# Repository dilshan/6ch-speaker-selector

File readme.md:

This project is a DIY six-channel stereo speaker selector based on *[STC15W201](https://www.stcmicro.com/datasheet/STC15W201S_Features.pdf)* MCU. The purpose of this electronic switch is to share a pair of speakers between six stereo audio systems.

To select each speaker channel, we use a couple of 12V DPDT relays. These relays interface to *74HC595* through a *ULN2001D*, 3-channel Darlington transistor array IC. 

The 6-channel speaker selector is an open-source project. This repository has all the schematics, PCB design files, and firmware source codes. 

The complete [documentation](https://github.com/dilshan/6ch-speaker-selector/wiki) of this project is in the [wiki section](https://github.com/dilshan/6ch-speaker-selector/wiki) of this repository. The PCB Gerber files and compiled binaries are also available in the [release section](https://github.com/dilshan/6ch-speaker-selector/releases) of this repository. The PCB of the 6-channel speaker selector can also order from the [PCBWay website](https://www.pcbway.com/project/shareproject/6_channel_stereo_speaker_selector_a32e4deb.html).

This is a [certified open hardware project](https://certification.oshwa.org/lk000013.html) and all the content of this project is distributed under the terms of the following license:

- Hardware License: [CERN-OHL-W 2.0](https://ohwr.org/cern_ohl_w_v2.txt)
- Software License: [MIT](https://github.com/dilshan/6ch-speaker-selector/blob/main/LICENSE)
- [Documentation](https://github.com/dilshan/6ch-speaker-selector/wiki) License: [CC BY 4.0](https://creativecommons.org/licenses/by/4.0/)

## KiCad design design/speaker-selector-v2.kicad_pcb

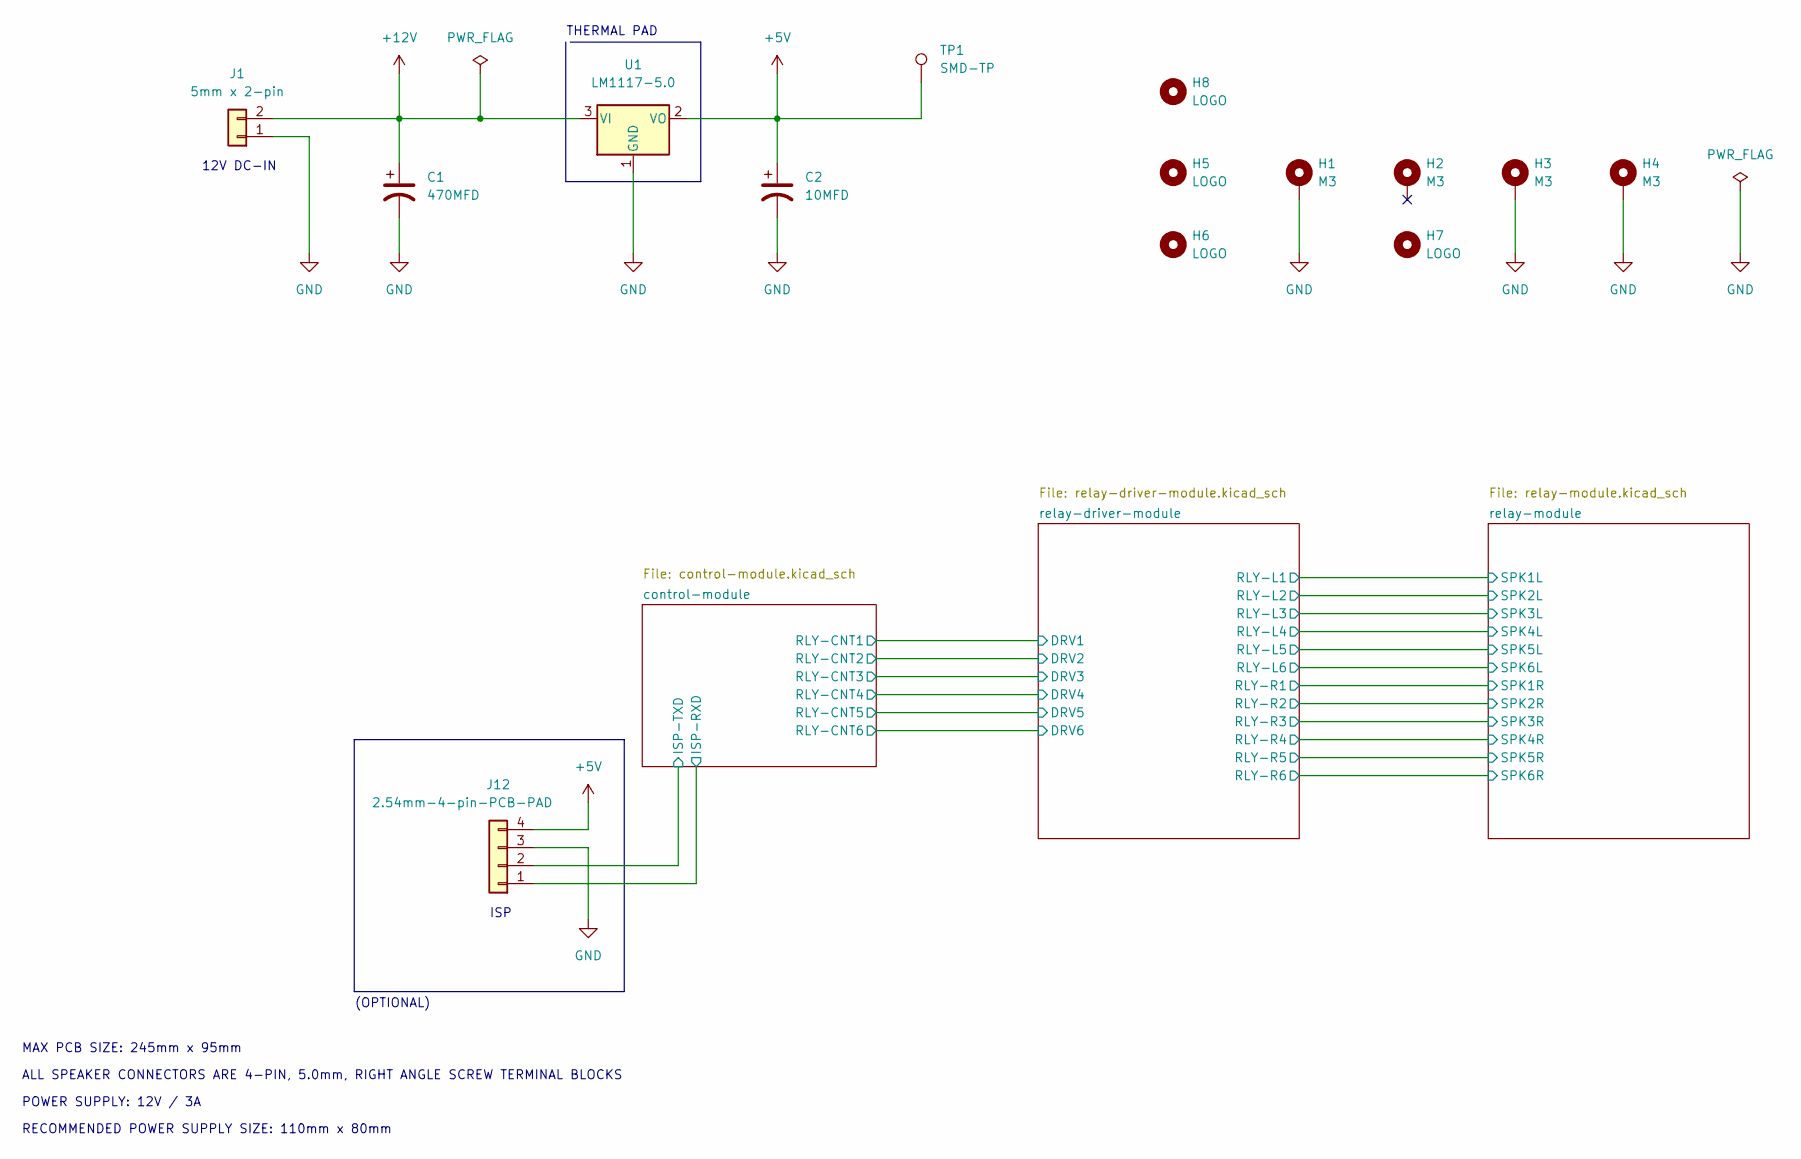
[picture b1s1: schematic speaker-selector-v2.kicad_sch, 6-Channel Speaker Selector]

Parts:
C1: 470MFD; CP_Radial_D10.0mm_P5.00mm
C2: 10MFD; CP_Radial_D5.0mm_P2.00mm
H1, H2, H3, H4: M3; MountingHole_2.5mm_Pad
H5: LOGO; 6ch-sss
H6: LOGO; pcbway
H7: LOGO; OSHW-Logo2_14.6x12mm_SilkScreen
H8: LOGO; 6ch-sss-large
J1: 5mm x 2-pin; TerminalBlock_Phoenix_MKDS-1,5-2_1x02_P5.00mm_Horizontal
J12: 2.54mm-4-pin-PCB-PAD; PinHeader_1x04_P2.54mm_Vertical
TP1: SMD-TP; TestPoint_Pad_D2.0mm
U1: LM1117-5.0; SOT-223-3_TabPin2

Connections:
+5V: C2.1, J12.4, TP1.1, U1.2 (VO); also elsewhere on the board
+12V: C1.1, J1.2, U1.3 (VI); also elsewhere on the board
/control-module/ISP-RXD: J12.1; also elsewhere on the board
/control-module/ISP-TXD: J12.2; also elsewhere on the board
GND: C1.2, C2.2, H1.1, H3.1, H4.1, J1.1, J12.3, U1.1 (GND); also elsewhere on the board

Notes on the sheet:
(OPTIONAL)
POWER SUPPLY: 12V / 3A
12V DC-IN
ISP
RECOMMENDED POWER SUPPLY SIZE: 110mm x 80mm
THERMAL PAD
ALL SPEAKER CONNECTORS ARE 4-PIN, 5.0mm, RIGHT ANGLE SCREW TERMINAL BLOCKS
MAX PCB SIZE: 245mm x 95mm

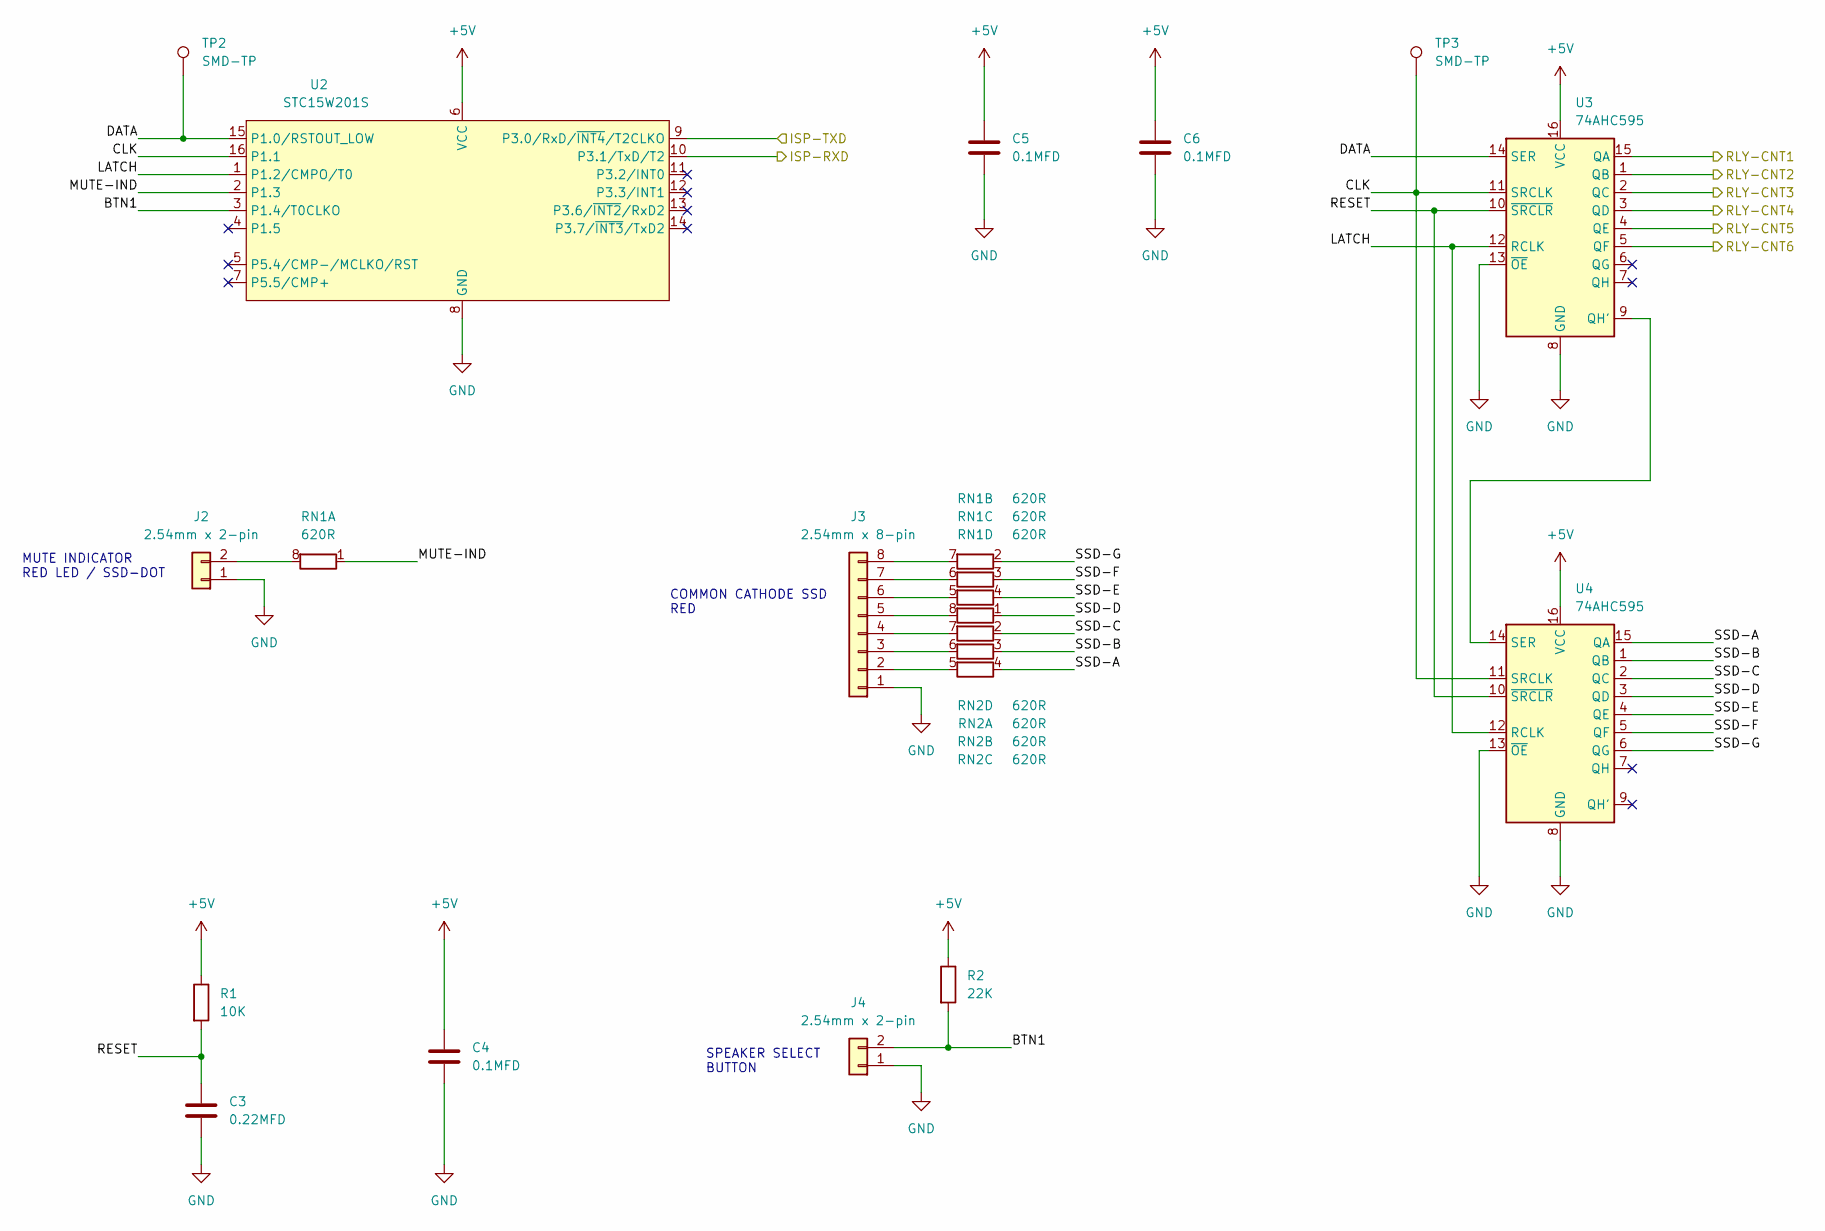
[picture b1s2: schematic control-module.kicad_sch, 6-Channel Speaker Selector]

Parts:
C3: 0.22MFD; C_0805_2012Metric_Pad1.18x1.45mm_HandSolder
C4, C5, C6: 0.1MFD; C_0805_2012Metric_Pad1.18x1.45mm_HandSolder
J2, J4: 2.54mm x 2-pin; JST_EH_B2B-EH-A_1x02_P2.50mm_Vertical
J3: 2.54mm x 8-pin; JST_EH_B8B-EH-A_1x08_P2.50mm_Vertical
R1: 10K; R_0805_2012Metric_Pad1.20x1.40mm_HandSolder
R2: 22K; R_0805_2012Metric_Pad1.20x1.40mm_HandSolder
RN1, RN2: 620R; R_Array_Concave_4x0603
TP2, TP3: SMD-TP; TestPoint_Pad_D2.0mm
U2: STC15W201S; SOP-16_3.9x9.9mm_P1.27mm
U3, U4: 74AHC595; SOP-16_3.9x9.9mm_P1.27mm

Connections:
+5V: C4.1, C5.1, C6.1, R1.1, R2.1, U2.6 (VCC), U3.16 (VCC), U4.16 (VCC); also elsewhere on the board
/control-module/BTN1: J4.2, R2.2, U2.3 (P1.4/T0CLKO)
/control-module/CLK: TP3.1, U2.16 (P1.1), U3.11 (SRCLK), U4.11 (SRCLK)
/control-module/DATA: TP2.1, U2.15 (P1.0/RSTOUT_LOW), U3.14 (SER)
/control-module/ISP-RXD: U2.10 (P3.1/TxD/T2); also elsewhere on the board
/control-module/ISP-TXD: U2.9 (P3.0/RxD/~INT4/T2CLKO); also elsewhere on the board
/control-module/LATCH: U2.1 (P1.2/CMPO/T0), U3.12 (RCLK), U4.12 (RCLK)
/control-module/MUTE-IND: RN1.1 (R1.1), U2.2 (P1.3)
/control-module/RESET: C3.1, R1.2, U3.10 (~SRCLR), U4.10 (~SRCLR)
/control-module/RLY-CNT1: U3.15 (QA); also elsewhere on the board
/control-module/RLY-CNT2: U3.1 (QB); also elsewhere on the board
/control-module/RLY-CNT3: U3.2 (QC); also elsewhere on the board
/control-module/RLY-CNT4: U3.3 (QD); also elsewhere on the board
/control-module/RLY-CNT5: U3.4 (QE); also elsewhere on the board
/control-module/RLY-CNT6: U3.5 (QF); also elsewhere on the board
/control-module/SSD-A: RN2.4 (R4.1), U4.15 (QA)
/control-module/SSD-B: RN2.3 (R3.1), U4.1 (QB)
/control-module/SSD-C: RN2.2 (R2.1), U4.2 (QC)
/control-module/SSD-D: RN2.1 (R1.1), U4.3 (QD)
/control-module/SSD-E: RN1.4 (R4.1), U4.4 (QE)
/control-module/SSD-F: RN1.3 (R3.1), U4.5 (QF)
/control-module/SSD-G: RN1.2 (R2.1), U4.6 (QG)
GND: C3.2, C4.2, C5.2, C6.2, J2.1, J3.1, J4.1, U2.8 (GND), U3.8 (GND), U3.13 (~OE), U4.8 (GND), U4.13 (~OE); also elsewhere on the board
unnamed: J2.2, RN1.8 (R1.2)
unnamed: J3.2, RN2.5 (R4.2)
unnamed: J3.3, RN2.6 (R3.2)
unnamed: J3.4, RN2.7 (R2.2)
unnamed: J3.5, RN2.8 (R1.2)
unnamed: J3.6, RN1.5 (R4.2)
unnamed: J3.7, RN1.6 (R3.2)
unnamed: J3.8, RN1.7 (R2.2)
unnamed: U3.9 (QH'), U4.14 (SER)

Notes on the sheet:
SPEAKER SELECT BUTTON
MUTE INDICATOR RED LED / SSD-DOT
COMMON CATHODE SSD RED

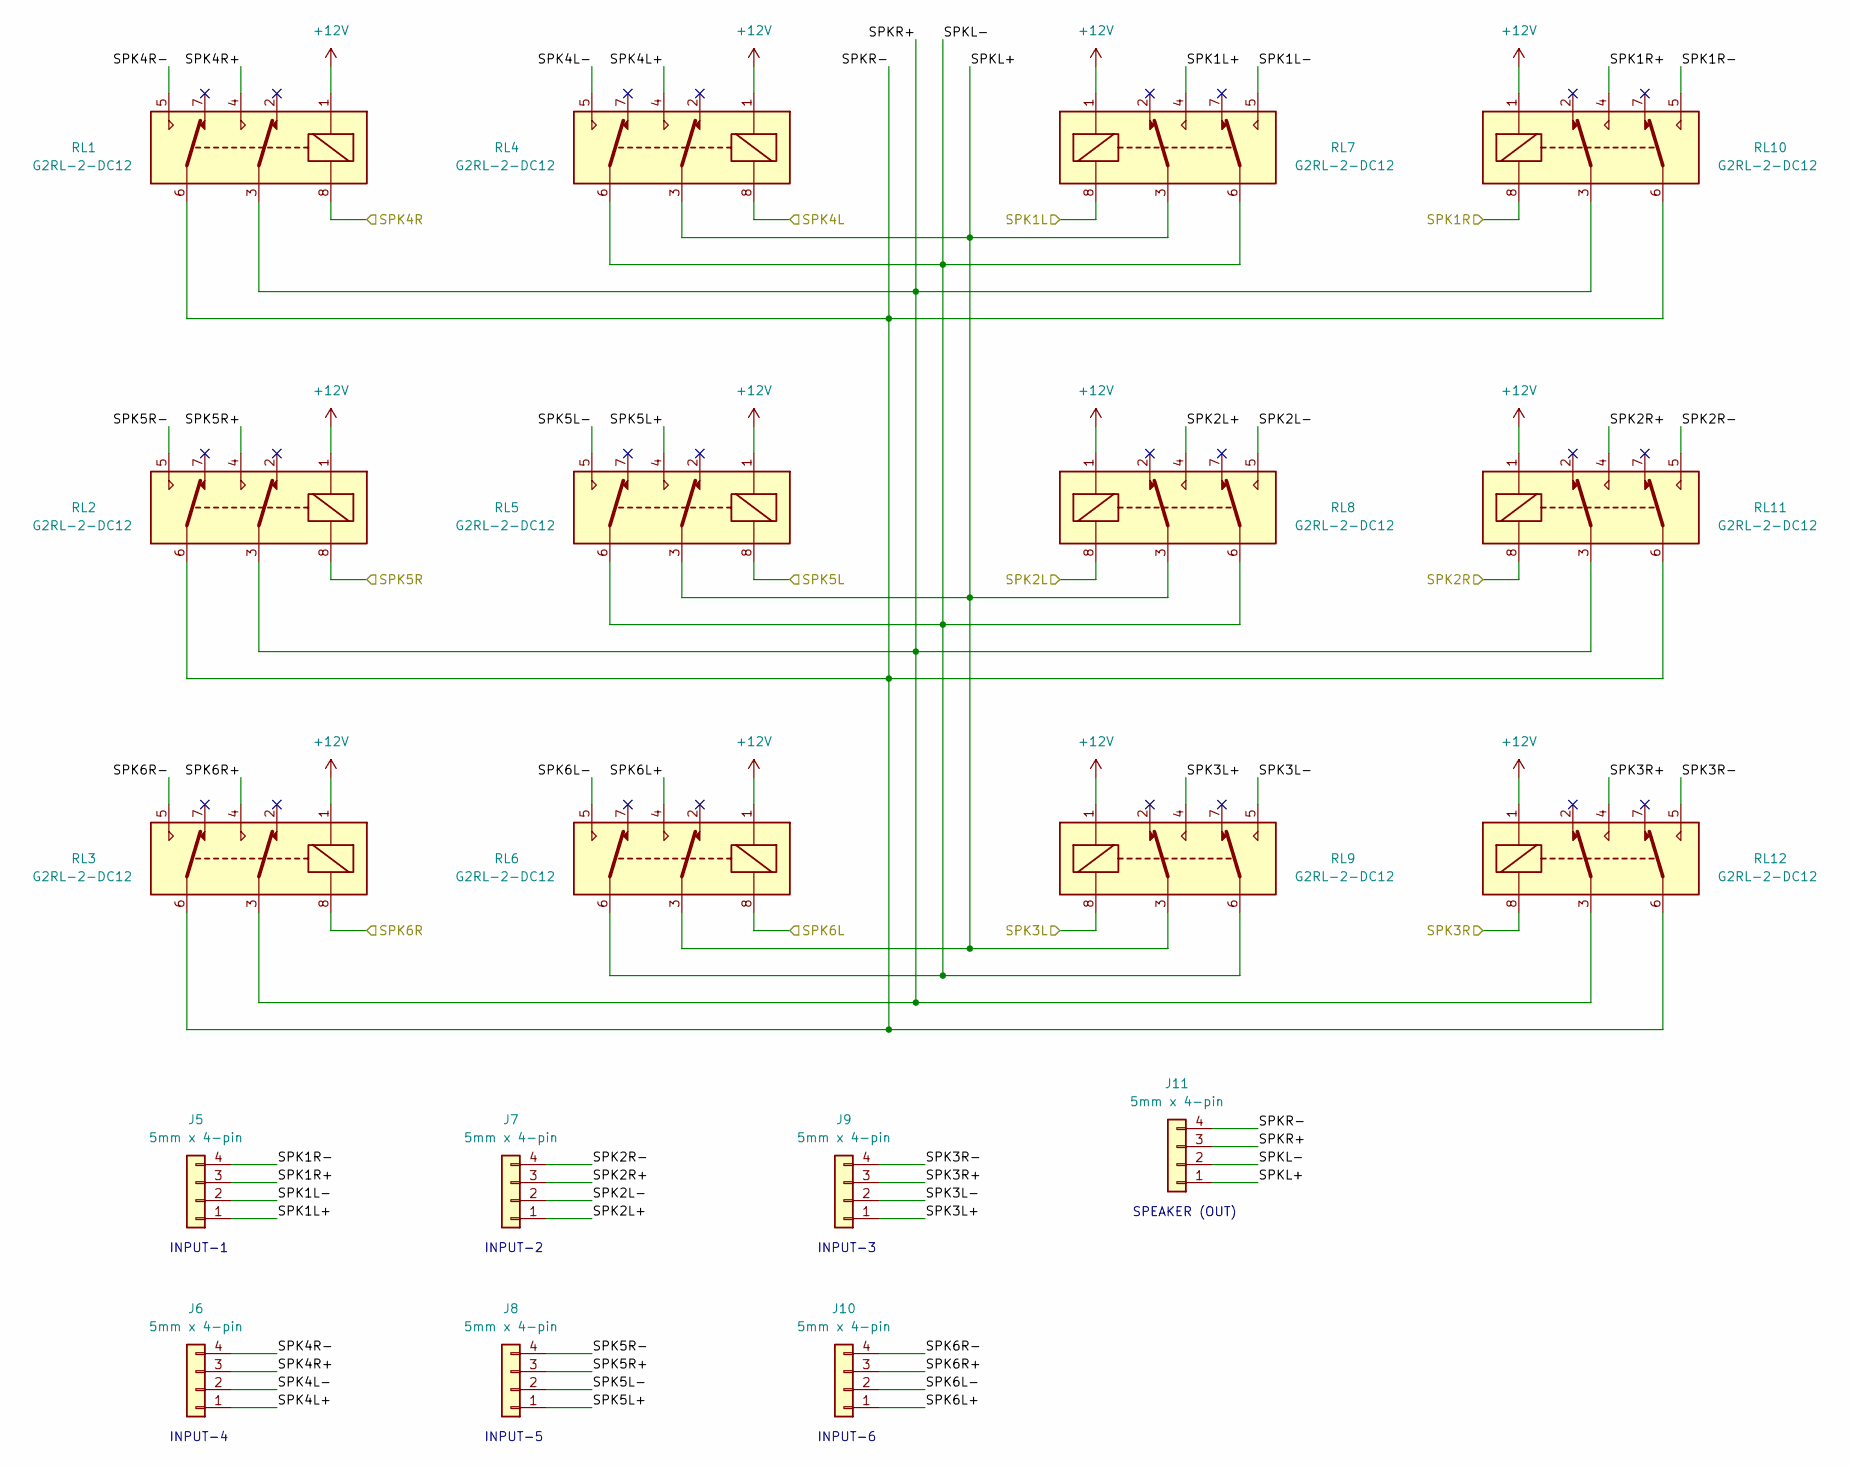
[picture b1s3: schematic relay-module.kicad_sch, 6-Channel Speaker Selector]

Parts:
J5, J6, J7, J8, J9, J10, J11: 5mm x 4-pin; PhoenixContact_MC_1,5_4-G-5.08_1x04_P5.08mm_Horizontal
RL1, RL2, RL3, RL4, RL5, RL6, RL7, RL8, RL9, RL10, RL11, RL12: G2RL-2-DC12; Relay_DPDT_Omron_G2RL

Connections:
+12V: RL1.1, RL2.1, RL3.1, RL4.1, RL5.1, RL6.1, RL7.1, RL8.1, RL9.1, RL10.1, RL11.1, RL12.1; also elsewhere on the board
/relay-driver-module/RLY-L1: RL7.8; also elsewhere on the board
/relay-driver-module/RLY-L2: RL8.8; also elsewhere on the board
/relay-driver-module/RLY-L3: RL9.8; also elsewhere on the board
/relay-driver-module/RLY-L4: RL4.8; also elsewhere on the board
/relay-driver-module/RLY-L5: RL5.8; also elsewhere on the board
/relay-driver-module/RLY-L6: RL6.8; also elsewhere on the board
/relay-driver-module/RLY-R1: RL10.8; also elsewhere on the board
/relay-driver-module/RLY-R2: RL11.8; also elsewhere on the board
/relay-driver-module/RLY-R3: RL12.8; also elsewhere on the board
/relay-driver-module/RLY-R4: RL1.8; also elsewhere on the board
/relay-driver-module/RLY-R5: RL2.8; also elsewhere on the board
/relay-driver-module/RLY-R6: RL3.8; also elsewhere on the board
/relay-module/SPK1L+: J5.1, RL7.4
/relay-module/SPK1L-: J5.2, RL7.5
/relay-module/SPK1R+: J5.3, RL10.4
/relay-module/SPK1R-: J5.4, RL10.5
/relay-module/SPK2L+: J7.1, RL8.4
/relay-module/SPK2L-: J7.2, RL8.5
/relay-module/SPK2R+: J7.3, RL11.4
/relay-module/SPK2R-: J7.4, RL11.5
/relay-module/SPK3L+: J9.1, RL9.4
/relay-module/SPK3L-: J9.2, RL9.5
/relay-module/SPK3R+: J9.3, RL12.4
/relay-module/SPK3R-: J9.4, RL12.5
/relay-module/SPK4L+: J6.1, RL4.4
/relay-module/SPK4L-: J6.2, RL4.5
/relay-module/SPK4R+: J6.3, RL1.4
/relay-module/SPK4R-: J6.4, RL1.5
/relay-module/SPK5L+: J8.1, RL5.4
/relay-module/SPK5L-: J8.2, RL5.5
/relay-module/SPK5R+: J8.3, RL2.4
/relay-module/SPK5R-: J8.4, RL2.5
/relay-module/SPK6L+: J10.1, RL6.4
/relay-module/SPK6L-: J10.2, RL6.5
/relay-module/SPK6R+: J10.3, RL3.4
/relay-module/SPK6R-: J10.4, RL3.5
/relay-module/SPKL+: J11.1, RL4.3, RL5.3, RL6.3, RL7.3, RL8.3, RL9.3
/relay-module/SPKL-: J11.2, RL4.6, RL5.6, RL6.6, RL7.6, RL8.6, RL9.6
/relay-module/SPKR+: J11.3, RL1.3, RL2.3, RL3.3, RL10.3, RL11.3, RL12.3
/relay-module/SPKR-: J11.4, RL1.6, RL2.6, RL3.6, RL10.6, RL11.6, RL12.6

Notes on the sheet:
INPUT-4
INPUT-6
INPUT-2
INPUT-3
INPUT-1
SPEAKER (OUT)
INPUT-5

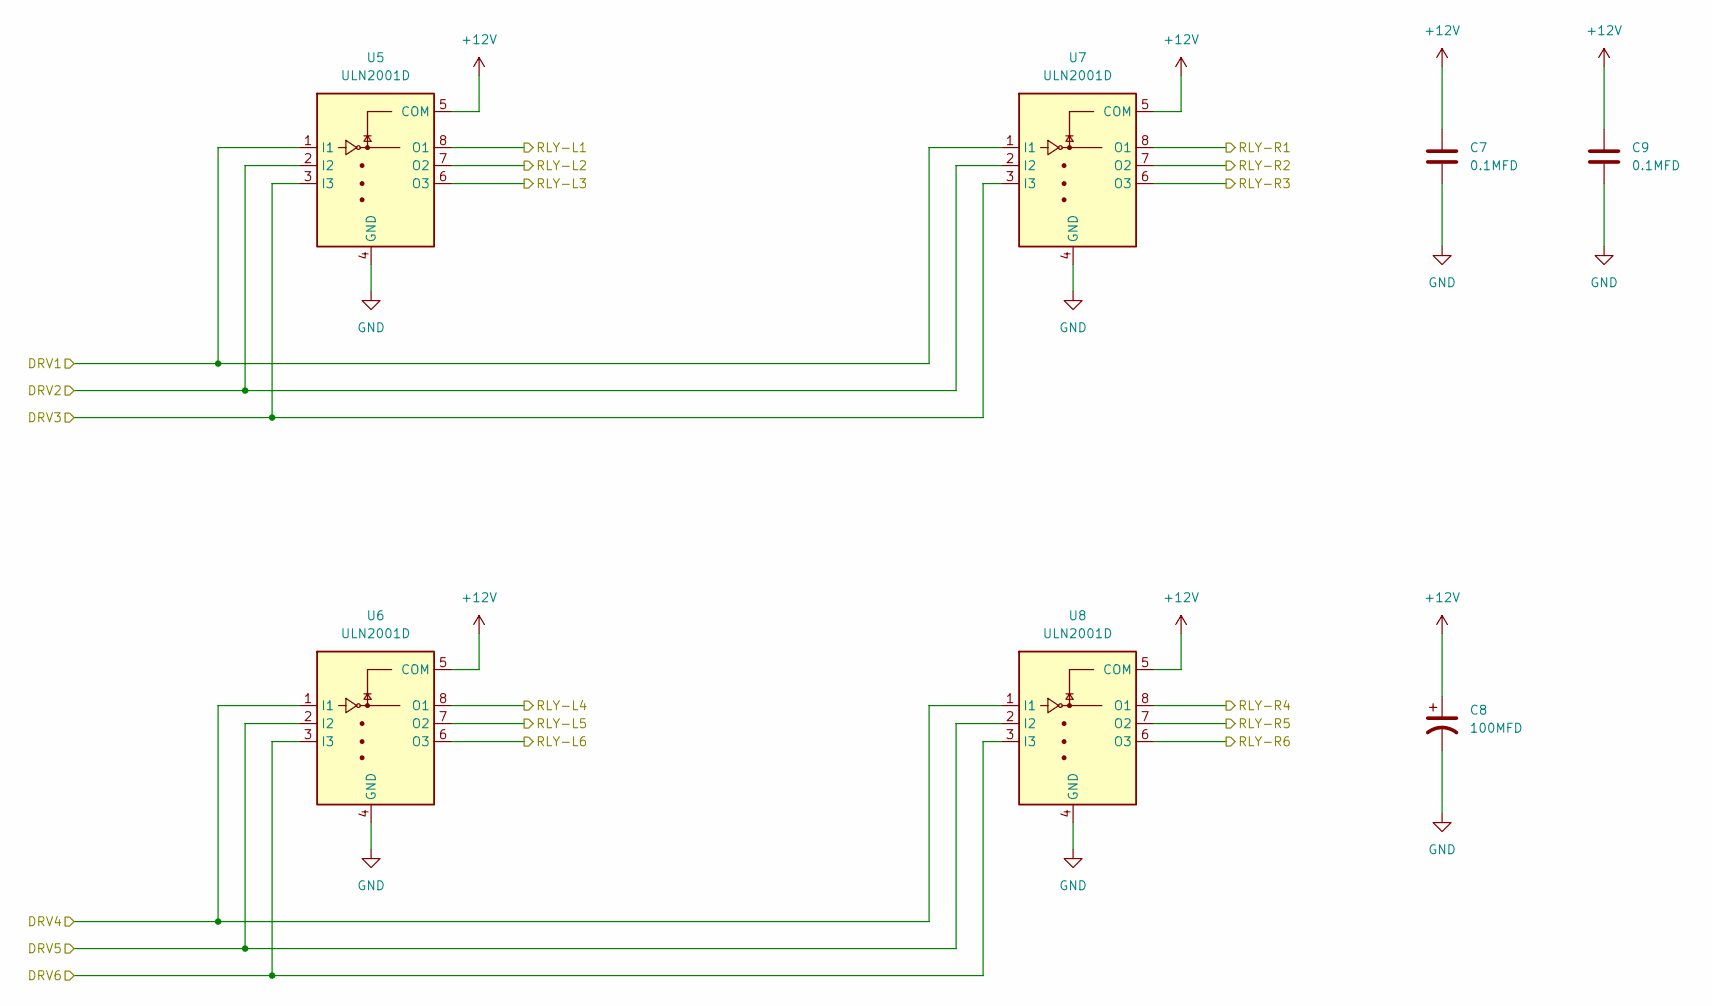
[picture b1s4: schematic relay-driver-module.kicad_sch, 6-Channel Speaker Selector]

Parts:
C7, C9: 0.1MFD; C_0805_2012Metric_Pad1.18x1.45mm_HandSolder
C8: 100MFD; CP_Radial_D6.3mm_P2.50mm
U5, U6, U7, U8: ULN2001D; SOP-8_3.9x4.9mm_P1.27mm

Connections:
+12V: C7.1, C8.1, C9.1, U5.5 (COM), U6.5 (COM), U7.5 (COM), U8.5 (COM); also elsewhere on the board
/control-module/RLY-CNT1: U5.1 (I1), U7.1 (I1); also elsewhere on the board
/control-module/RLY-CNT2: U5.2 (I2), U7.2 (I2); also elsewhere on the board
/control-module/RLY-CNT3: U5.3 (I3), U7.3 (I3); also elsewhere on the board
/control-module/RLY-CNT4: U6.1 (I1), U8.1 (I1); also elsewhere on the board
/control-module/RLY-CNT5: U6.2 (I2), U8.2 (I2); also elsewhere on the board
/control-module/RLY-CNT6: U6.3 (I3), U8.3 (I3); also elsewhere on the board
/relay-driver-module/RLY-L1: U5.8 (O1); also elsewhere on the board
/relay-driver-module/RLY-L2: U5.7 (O2); also elsewhere on the board
/relay-driver-module/RLY-L3: U5.6 (O3); also elsewhere on the board
/relay-driver-module/RLY-L4: U6.8 (O1); also elsewhere on the board
/relay-driver-module/RLY-L5: U6.7 (O2); also elsewhere on the board
/relay-driver-module/RLY-L6: U6.6 (O3); also elsewhere on the board
/relay-driver-module/RLY-R1: U7.8 (O1); also elsewhere on the board
/relay-driver-module/RLY-R2: U7.7 (O2); also elsewhere on the board
/relay-driver-module/RLY-R3: U7.6 (O3); also elsewhere on the board
/relay-driver-module/RLY-R4: U8.8 (O1); also elsewhere on the board
/relay-driver-module/RLY-R5: U8.7 (O2); also elsewhere on the board
/relay-driver-module/RLY-R6: U8.6 (O3); also elsewhere on the board
GND: C7.2, C8.2, C9.2, U5.4 (GND), U6.4 (GND), U7.4 (GND), U8.4 (GND); also elsewhere on the board

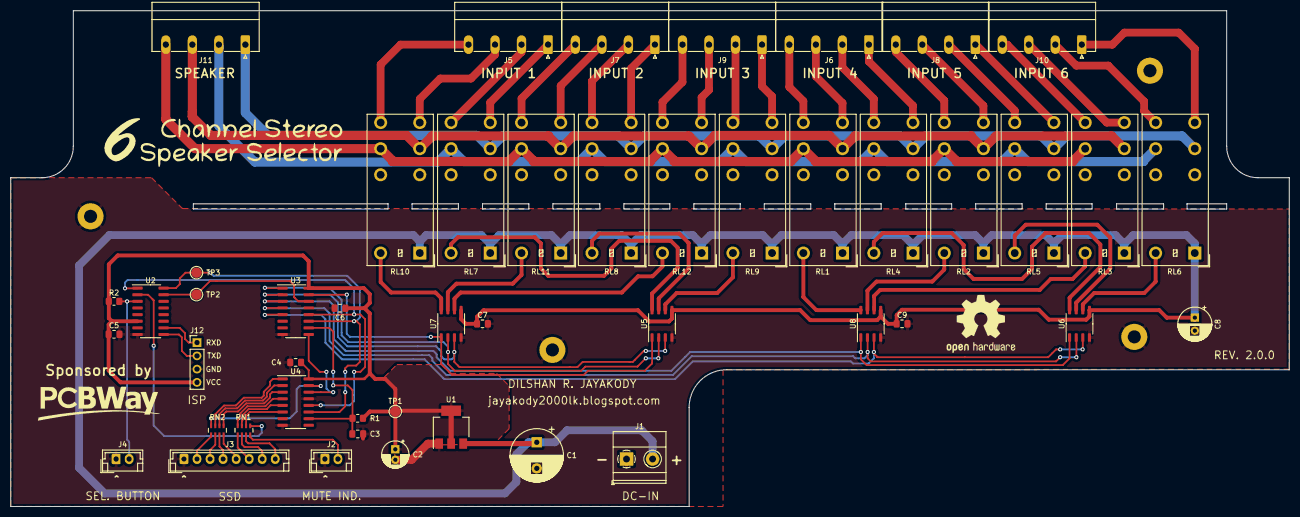
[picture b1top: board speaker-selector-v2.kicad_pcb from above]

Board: 2 copper layers, 245.0 x 95.0 mm, 56 parts (1 on the bottom side), 73 nets.

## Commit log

2022-12-28 Initial version of STC15W201S firmware.
2022-12-28 Add initial version of design files.
2022-12-28 Create firmware LICENSE file.
2022-12-28 Initial version of readme file.
2022-12-29 Correct Darlinton array part number.
2022-12-29 Add wiring layout project.
2022-12-30 Add PDF version of the schematic diagram.
2022-12-30 Update documentation, release page, and license page links in readme file.
2022-12-30 Add YouTube video thumbnail.
2022-12-30 Add YouTube video link into readme.md file.
2022-12-30 Update PCBWay PCB purchase link.
2023-01-17 Add OSHWA link to the readme.md file.

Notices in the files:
design/speaker-selector-v2.kicad_pcb:
Licensed under CERN-OHL-W 2.0
